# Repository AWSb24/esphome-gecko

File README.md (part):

Home Assistant integration for Gecko spa systems. The ESP32 drives the spa's 5V I2C bus directly through a bidirectional logic level converter - no Arduino in the middle. The reference build uses a Seeed Studio XIAO ESP32-C3. Tested together with a Gecko IN.YE-3-H3.0 (YE-3-CE) spa controller. Feel free to combine with my home assistant integration for smart heating based on electricty price [Smart Spa Heating Integration](https://github.com/zteifel/smart-spa-heating).

## In this fork (in.YE-5 support)

This fork builds on kcembrey's `direct-i2c` branch and adds what an **in.YE-5-H3.0** (config 65 / status 66) needs once the in.touch 2 cloud module is retired:

| Feature | What it does | Docs |
|---|---|---|
| Clock sync | Keeps the spa's clock set from SNTP or Home Assistant, which the in.touch used to do | [Clock sync](#clock-sync) |
| Keypad lock | UNLOCK / PARTIAL / FULL as a select in Home Assistant | [Keypad lock](#keypad-lock) |
| ISO1540 isolation | Galvanic isolation between ESP32 and spa bus instead of a BSS138 level converter | [in.YE-5 with an ISO1540 isolator](#inye-5-with-an-iso1540-isolator) |
| WT32-ETH01 | Wired Ethernet instead of Wi-Fi | [WT32-ETH01 with ATV32 drives](#wt32-eth01-with-atv32-drives-on-the-pumps) |
| Pump drives | Altivar 32 / 320 frequency drives over Modbus RTU for soft start and speed control (three-phase motors only) | [WT32-ETH01 with ATV32 drives](#wt32-eth01-with-atv32-drives-on-the-pumps) |
| Carrier board | KiCad PCB: WT32-ETH01, ISO1540, RS485, CO-port header | [`hardware/`](hardware/) |

Ready-made configs:

| File | Board | Network | Extras |
|---|---|---|---|
| [`esphome/spa-controller-in-ye-5-iso1540.yaml`](esphome/spa-controller-in-ye-5-iso1540.yaml) | ESP32 DevKit + ISO1540 | Wi-Fi | Clock sync, keypad lock |
| [`esphome/spa-controller-wt32-eth01-atv32.yaml`](esphome/spa-controller-wt32-eth01-atv32.yaml) | WT32-ETH01 + ISO1540 + RS485 | Ethernet | Plus 3 pump drives via [`esphome/packages/atv32-pump.yaml`](esphome/packages/atv32-pump.yaml) |

**ESPHome version:** the component is an external component and builds against whatever ESPHome you run. It has been checked with ESPHome 2026.10.2; direct I2C on ESP-IDF needs ESP-IDF 5.4 or newer. To get a clear error on an older install, add `min_version: 2026.10.0` under `esphome:`.

On the in.YE-5 the commands use geckolib's SET_VALUE / KEY_PRESS payloads with the pack's own config/status versions, and the memory map matches geckolib's `inyt-cfg-65` / `inyt-log-66`. Status, setpoint, light and pumps 1-3 decode as on the in.YE-3; control from the ESP32 is still to be confirmed on a running in.YE-5.

## Architecture

```
┌──────────────────┐              ┌──────────────────┐             ┌─────────────┐
│      ESP32       │   3.3V I2C   │  Level Converter │   5V I2C    │  Gecko Spa  │
│                  │◄────────────►│    (BSS138 x2)   │◄───────────►│             │
│ - I2C slave      │  SDA / SCL   │                  │   (0x17)    │             │
│   (listening)    │              │  Bidirectional,  │             │             │
│ - I2C master     │              │  open-drain safe │             │             │
│   (short bursts) │              │                  │             │             │
│ - Protocol logic │              │                  │             │             │
│ - Home Assistant │              │                  │             │             │
│ - OTA updates    │              │                  │             │             │
└──────────────────┘              └──────────────────┘             └─────────────┘
```

**Key Design Decision:** The Gecko bus is multi-master and both ends answer to address `0x17`, so the ESP32 cannot stay in one role. It sits in I2C **slave** mode listening to the spa, and flips to **master** mode for the few milliseconds it takes to push a command or a handshake ACK out, then goes straight back to listening. That is exactly what the Arduino proxy used to do internally - it now happens on the ESP32 itself, and all protocol encoding/decoding stays where it always was, on a chip you can update over WiFi (OTA).

Dropping the Arduino also removes the failure mode where the spa restarts but the Arduino does not (or the other way round) and the link stays dead until something power-cycles the proxy. There is no second processor to fall out of sync: when the bus goes quiet the ESP32 reinitialises its own I2C peripheral, which includes the standard nine-clock bus recovery.

> **Still running the Arduino proxy?** It is still supported - see [Legacy: Arduino I2C Proxy](#legacy-arduino-i2c-proxy).

## Table of Contents

1. [Installation](#installation)
2. [Hardware Build](#hardware-build)
3. [Configuration Reference](#configuration-reference)
4. [I2C Protocol](#i2c-protocol)
5. [Legacy: Arduino I2C Proxy](#legacy-arduino-i2c-proxy)
6. [Buy me a coffee](#buy-me-a-coffee)
7. [TODO](#todo)
8. [Troubleshooting](#troubleshooting)
9. [Credits](#credits)

---

## Installation

### Quick Start

1. **Set up hardware** - See [Hardware Build](#hardware-build) section below

2. **Nothing to flash but the ESP32** - the level converter is passive. If you are migrating from the Arduino proxy, unplug the Arduino and wire the converter in its place; see [Hardware Build](#hardware-build).

3. **Create a secrets.yaml file** with your credentials:
   ```yaml
   wifi_ssid: "YourWiFiName"
   wifi_password: "YourWiFiPassword"
   api_encryption_key: "generate-with-openssl-rand-base64-32"
   ota_password: "your-ota-password"
   ```
   Generate the API key with: `openssl rand -base64 32`

4. **Create your ESPHome configuration** - This component can be installed directly from GitHub:

```yaml
substitutions:
  device_name: spa-controller

esphome:
  name: ${device_name}
  friendly_name: Spa Controller

esp32:
  # Seeed Studio XIAO ESP32-C3 - the generic C3 definition works for it
  board: esp32-c3-devkitm-1
  framework:
    type: arduino  # esp-idf works too - see Configuration Reference

# Import Gecko Spa component from GitHub
external_components:
  - source: github://zteifel/esphome-gecko
    components: [gecko_spa]

logger:
  level: DEBUG

wifi:
  ssid: !secret wifi_ssid
  password: !secret wifi_password

api:
  encryption:
    key: !secret api_encryption_key

ota:
  platform: esphome
  password: !secret ota_password

# Gecko Spa component - direct connection to the spa I2C bus.
# XIAO D0/D2. See Hardware Build for why these and not D4/D5.
gecko_spa:
  id: spa
  sda: GPIO2
  scl: GPIO4

# Climate control
climate:
  - platform: gecko_spa
    gecko_spa_id: spa
    name: "Spa"

# Switches
switch:
  - platform: gecko_spa
    gecko_spa_id: spa
    type: light
    name: "Spa Light"
    icon: "mdi:lightbulb"

  - platform: gecko_spa
    gecko_spa_id: spa
    type: pump1
    name: "Spa Pump"
    icon: "mdi:pump"

  - platform: gecko_spa
    gecko_spa_id: spa
    type: circulation
    name: "Spa Circulation"
    icon: "mdi:rotate-3d-variant"

# Program selector
select:
  - platform: gecko_spa
    gecko_spa_id: spa
    name: "Spa Program"
    icon: "mdi:format-list-bulleted"

# Status sensors
binary_sensor:
  - platform: gecko_spa
    gecko_spa_id: spa
    type: standby
    name: "Spa Standby"
    icon: "mdi:power-standby"

  - platform: gecko_spa
    gecko_spa_id: spa
    type: connected
    name: "Spa Connected"
    device_class: connectivity

# Spa internal clock and maintenance reminder due dates
text_sensor:
  - platform: gecko_spa
    gecko_spa_id: spa
    type: spa_time
    name: "Spa Time"
    icon: "mdi:clock-outline"

  - platform: gecko_spa
    gecko_spa_id: spa
    type: rinse_filter
    name: "Rinse Filter Due"
    icon: "mdi:air-filter"

  - platform: gecko_spa
    gecko_spa_id: spa
    type: clean_filter
    name: "Clean Filter Due"
    icon: "mdi:air-filter"

  - platform: gecko_spa
    gecko_spa_id: spa
    type: change_water
    name: "Change Water Due"
    icon: "mdi:water-sync"

  - platform: gecko_spa
    gecko_spa_id: spa
    type: spa_checkup
    name: "Spa Checkup Due"
    icon: "mdi:wrench-clock"
```

5. **Flash and add to Home Assistant**:
   ```bash
   esphome run your-config.yaml
   ```

6. The device will appear in Home Assistant under **Settings → Devices & Services → ESPHome**

### Home Assistant Entities

After installation, you'll have these entities:

| Entity | Type | Description |
|--------|------|-------------|
| Spa | Climate | Temperature control with current/target display |
| Spa Light | Switch | Control spa light |
| Spa Pump 1 | Switch | Control main pump |
| Spa Circulation | Switch | Control circulation pump |
| Spa Program | Select | Choose program (Away, Standard, Energy, Super Energy, Weekend) |
| Spa Keypad Lock | Select | UNLOCK / PARTIAL / FULL (`type: lock`) |
| Set Spa Clock | Button | `id(spa).sync_clock()` - with `clock_sync` configured |
| Spa Standby | Binary Sensor | Standby mode status |
| Spa Connected | Binary Sensor | Connection status to spa |
| Spa Time | Text Sensor | Spa's internal clock (DD/MM HH:MM:SS) |
| Spa Rinse Filter Due | Text Sensor | Due date for filter rinse (YYYY-MM-DD) |
| Spa Clean Filter Due | Text Sensor | Due date for filter clean (YYYY-MM-DD) |
| Spa Change Water Due | Text Sensor | Due date for water change (YYYY-MM-DD) |
| Spa Checkup Due | Text Sensor | Due date for spa checkup (YYYY-MM-DD) |
| Refresh Spa Status | Button | Manually request status update |
| Reconnect Spa Bus | Button | Reinitialise the I2C peripheral and recover the bus |

---

## Hardware Build

The reference build is a **Seeed Studio XIAO ESP32-C3**. Other ESP32 boards work too - see [Other boards](#other-boards).

### Components Required

| Component | Description | Notes |
|-----------|-------------|-------|
| Seeed Studio XIAO ESP32-C3 | WiFi microcontroller | Reference board. Any ESP32 works, on either framework |
| Bidirectional logic level converter | 3.3V <-> 5V, 2 channels minimum | **Must be the MOSFET (BSS138) type.** See the warning below |
| 2 x 220Ω resistors | Series protection for the I2C pins | Recommended - see [Protecting the ESP32 pins](#protecting-the-esp32-pins) |
| Dupont wires | Various | Connections between board, converter and spa |

> **The converter type matters.** I2C is an open-drain bus: both ends pull the line low and pull-up resistors bring it back high. Only the passive MOSFET converters (BSS138, or a TXS010x) can pass that. A push-pull converter such as the **TXB0104 will not work** on I2C, and neither will a resistor voltage divider - that is fine for one-way UART, but it cannot pass a line the far end is holding down.

### Pin Connections

#### XIAO ESP32-C3 to Level Converter (low-voltage side)

| XIAO Pin | GPIO | Converter Pin | Notes |
|----------|------|---------------|-------|
| D0 | GPIO2 | LV1 | I2C data (SDA), via 220Ω |
| D2 | GPIO4 | LV2 | I2C clock (SCL), via 220Ω |
| 3V3 | - | LV | Reference for the low side. **Must be 3.3V, never 5V** |
| GND | - | GND | Common ground |

#### Level Converter to Spa (high-voltage side)

Pin numbers are on the spa's CO port, as shown in the pinout picture below.

| Converter Pin | Spa CO Port | Notes |
|---------------|-------------|-------|
| HV1 | SDA (pin 3) | I2C data, 5V side |
| HV2 | SCL (pin 2) | I2C clock, 5V side |
| HV | 5V (pin 4) | Reference for the high side |
| GND | GND (pin 8) | Common ground required |

**Why D0/D2 and not D4/D5?** D4/D5 (GPIO6/GPIO7) are the XIAO's labelled SDA/SCL, and on a healthy board they are the better choice because they are not strapping pins. The reference build moved to D0/D2 after GPIO6/GPIO7 were damaged by 5V from the old Arduino proxy wiring. GPIO2 is a C3 strapping pin, so ESPHome prints a warning about it; the I2C pull-ups hold it high at reset, which is the state it needs.

**Pull-ups:** the spa bus already carries its own pull-ups to 5V, and BSS138 breakout boards carry 10k pull-ups on both sides. Do not add more.

**Power:** the spa's 5V rail can supply the converter's HV reference, but do not run the ESP32 off it - the spa rates that line at 125mA, and WiFi bursts go above that. Use USB or a separate supply.

### Protecting the ESP32 pins

A correctly wired BSS138 never lets the ESP32 side rise above its 3.3V reference, so the pins are safe by design. These guard against the ways that can go wrong:

- **220Ω in series with each I2C line, at the ESP32 end.** If 5V ever reaches the line, this limits the current into the pin's clamp diodes to a few mA, which the pin survives. It makes no practical difference to I2C at 100kHz. Stay at 220Ω or below: when the ESP32 pulls the line low, the spa-side pull-up current flows through this resistor too, and a larger value lifts the "low" voltage.
- **Meter the converter before connecting the ESP32.** LV must read 3.3V and HV 5V. LV accidentally on 5V is the one miswiring that puts 5V straight onto the ESP32 pins through the converter's pull-ups.
- **Optional: a TVS/ESD array (~5-6V, e.g. SRV05-4) on the spa side**, where the cable lands. Pumps and heaters make a spa an electrically noisy place, and Gecko's own in.touch-2 uses a TVS plus series resistors (see the note in the pinout picture).
- **Optional: full galvanic isolation.** An **ISO1540** or **ADuM1250** can replace the BSS138: it level-shifts and isolates, so the spa and ESP32 grounds are no longer joined. Use those parts, **not the ISO1541/ADuM1251**, which pass SCL in one direction only - the spa drives the clock too, so they would break this multi-master bus. Their ESP32-side low level also sits a little above 0V by design, so bench-test before sealing the enclosure.

### Wiring Diagram
Credits to agittins for the pictures

```
              ┌────────────────────────────────┐
              │   Gecko Spa CO port (pin no.)  │
              │                                │
              │    SDA     SCL     5V     GND  │
              │    (3)     (2)     (4)    (8)  │
              └─────┬───────┬───────┬──────┬───┘
                    │       │       │      │
              ┌─────┴───────┴───────┴──────┴───┐
              │    HV1     HV2     HV     GND  │
              │      Logic Level Converter     │
              │     (BSS138, bidirectional)    │
              │    LV1     LV2     LV     GND  │
              └─────┬───────┬───────┬──────┬───┘
                    │       │       │      │
                 [220Ω]  [220Ω]     │      │
                    │       │       │      │
              ┌─────┴───────┴───────┴──────┴───┐
              │    D0      D2     3V3     GND  │
              │  (GPIO2) (GPIO4)               │
              │      Seeed XIAO ESP32-C3       │
              └────────────────────────────────┘
```

### Other boards

Direct I2C works on any ESP32, with either framework. These example configs compile but have not been run against a spa:

- [`esphome/spa-controller-feather-s2.yaml`](esphome/spa-controller-feather-s2.yaml) - Adafruit Feather ESP32-S2 on GPIO3/GPIO4 (the pins labelled SDA/SCL). That board gates power to its on-board I2C pull-ups behind GPIO7, which the config drives high on boot.
- [`esphome/spa-controller-olimex.yaml`](esphome/spa-controller-olimex.yaml) - Olimex ESP32-POE-ISO on GPIO13/GPIO14. See [the Olimex guide](docs/olimex-poe-setup.md).
- [`esphome/spa-controller-in-ye-5-iso1540.yaml`](esphome/spa-controller-in-ye-5-iso1540.yaml) - ESP32 DevKit on GPIO21/GPIO22 behind an ISO1540 isolator. See [in.YE-5 with an ISO1540 isolator](#inye-5-with-an-iso1540-isolator).
- [`esphome/spa-controller-wt32-eth01-atv32.yaml`](esphome/spa-controller-wt32-eth01-atv32.yaml) - WT32-ETH01 on IO4/IO32 behind an ISO1540, with RS485 for pump drives. See [WT32-ETH01 with ATV32 drives](#wt32-eth01-with-atv32-drives-on-the-pumps) and the carrier board in [`hardware/`](hardware/).

---

## Configuration Reference

### `gecko_spa` options

| Option | Default | Description |
|--------|---------|-------------|
| `sda` | *(required for direct I2C)* | GPIO carrying I2C data to the level converter |
| `scl` | *(required for direct I2C)* | GPIO carrying I2C clock to the level converter |
| `i2c_bus` | `0` | Which I2C peripheral to use. Change it only if something else in your config already claims bus 0. The ESP32-C3 has only one, so it must be `0` there |
| `address` | `0x17` | Bus address. Both the spa and the controller answer to this |
| `frequency` | `100kHz` | Bus speed. The spa runs standard mode; leave it alone unless you know otherwise |
| `notif_date_format` | `D-M-Y` | Swap to `Y-M-D` if the maintenance reminder dates look wrong |
| `min_temperature` | `26°C` | Lowest setpoint Home Assistant will offer and send, down to `10°C` |
| `max_temperature` | `40°C` | Highest setpoint Home Assistant will offer and send, up to `41.1°C` (106 °F). Gecko panels only go above 40 °C by holding the up key |
| `quiet_time` | - | Hold the pumps off every night - see [Quiet time](#quiet-time) |
| `clock_sync` | - | Keep the spa's clock set from an ESPHome time source - see [Clock sync](#clock-sync) |
| `uart_id` | - | Legacy Arduino proxy mode. Mutually exclusive with `sda`/`scl` |
| `reset_pin` | - | Legacy Arduino proxy mode only - the GPIO wired to the Arduino's RST pin |

Direct I2C mode works on both ESP32 frameworks, and picks the I2C slave backend to match:

| Framework | Backend | Notes |
|-----------|---------|-------|
| `arduino` | The Arduino core's I2C slave HAL | The one the reference build has been run against a spa on |
| `esp-idf` | ESP-IDF's I2C slave driver, version 2 | Needs ESP-IDF 5.4 or newer. On 5.x the component enables `CONFIG_I2C_ENABLE_SLAVE_DRIVER_VERSION_2` itself: version 1 cannot tell where one transaction ends and the next begins, and this protocol identifies messages by their length. ESP-IDF 6 has only version 2, the same API, so nothing needs enabling there |

The `Transport:` line in the boot log says which one is running. On a XIAO ESP32-C3, esp-idf builds about 54 KB smaller in flash and saves about 3 KB of RAM.

**Switching an existing device between frameworks:** both frameworks give the app the same two OTA slots, at the same size and position, so an OTA update can carry the switch. OTA never rewrites the partition table, though, so the device keeps its old table until its next USB flash. That is harmless: the only differences come after the app slots (the Arduino layout has a slightly smaller NVS plus two partitions the esp-idf build ignores).

### Lambdas

| Call | Description |
|------|-------------|
| `id(spa).request_status()` | Send a GO immediately, prompting a fresh handshake and status dump |
| `id(spa).recover_link()` | Reinitialise the link: I2C peripheral reset (direct mode) or Arduino reset pulse (proxy mode) |
| `id(spa).reset_arduino()` | Alias of `recover_link()`, kept so older configs keep working |
| `id(spa).pause_quiet_time(120)` | Let the pumps run for the next 120 minutes even inside quiet time; `0` resumes quiet time now |
| `id(spa).start_quiet_time(120)` | Start quiet time now, outside the window too, for the next 120 minutes (a run that reaches the window carries on into it); `0` goes back to the schedule |
| `id(spa).sync_clock()` | Set the spa's clock from the `clock_sync` time source now |
| `id(spa).send_lock_command(1)` | Keypad lock: `0` unlocked, `1` partial, `2` full |
| `id(spa).hold_standby(15)` | Hold the spa in standby for the next 15 minutes, whatever the time; call again to extend, `0` releases - see [Standby hold](#standby-hold) |

### Quiet time

Outside its filter cycles a spa still runs its pumps now and then, mostly to circulate water past the heater's temperature probe. The only way to stop that is standby - the panel's Maintenance mode, which turns every pump off for a while (30 minutes from the panel). Quiet time puts the spa into that same standby every night and keeps it there:

```yaml
gecko_spa:
  # ...
  quiet_time:
    time_id: ha_time       # your time: component; optional if you have just one
    start: "21:00"
    end: "09:00"
    min_water_temperature: 10°C   # optional, default 10°C
```

- Each standby runs on the spa's own timer for 60 minutes and is topped up before it ends, so a crash or reboot can never keep the pumps off for more than an hour.
- At `end` - or when paused - quiet time takes the spa out of the standby it started. It never ends a Maintenance run you started from the panel outside quiet time.
- **Standby stops the heater too.** The water cools overnight and heats again after `end`. If it ever falls below `min_water_temperature`, quiet time gives up until the next night.
- Turn on a pump during quiet time and quiet time will put the spa back in standby within about a minute. Pause it first.

Buttons to pause it or start it early, and a sensor showing whether it is in force:

```yaml
button:
  - platform: template
    name: "Spa Quiet Time Off (2 h)"
    icon: "mdi:volume-high"
    on_press:
      - lambda: id(spa).pause_quiet_time(120);

  - platform: template
    name: "Spa Quiet Time On (2 h)"     # start it early, or for a while during the day
    icon: "mdi:sleep"
    on_press:
      - lambda: id(spa).start_quiet_time(120);

binary_sensor:
  - platform: gecko_spa
    gecko_spa_id: spa
    type: quiet_time
    name: "Spa Quiet Time"
```

Quiet time needs the standby timer's position in the status block, which is mapped for status version 51 and later.

### Standby hold

`hold_standby(minutes)` puts the spa in the same standby on demand - for example to shed load when a battery inverter is close to its limit, since standby stops the heater (about 4 kW on a 240 V pack) and every pump. Each call extends the hold; `0` releases it. A hold that is not renewed lapses by itself, so a lost release never keeps the spa off for long.

Expose it to Home Assistant as an action, plus a sensor showing when a hold is in force:

```yaml
api:
  actions:
    - action: spa_standby_hold          # esphome.<device name>_spa_standby_hold in Home Assistant
      variables:
        minutes: int
      then:
        - lambda: id(spa).hold_standby(minutes);

binary_sensor:
  - platform: gecko_spa
    gecko_spa_id: spa
    type: standby_hold
    name: "Spa Standby Hold"
```

A hold works with or without `quiet_time`. Releasing it takes the spa out of standby only if the hold put it there and quiet time does not want it: a Maintenance run started from the panel is left alone.

### Water-care programs

On spas whose panel has water-care programs (Away, Standard, Energy, Super Energy, Weekend), each with its own filter times and days, the program - not the spa's internal filter schedule - starts and stops filtration. The spa reports this as `FilterAccess = REMOTE`. The program schedules themselves live in the panel, which the ESP32 cannot see from the spa's communication port, so they cannot be read or edited from Home Assistant.

What you can do from Home Assistant:

- **Switch program** with the `select` platform.
- **See what the program is doing**, read-only:

```yaml
text_sensor:
  - platform: gecko_spa
    gecko_spa_id: spa
    type: filtration          # Idle / Stop / Start / New / Active
    name: "Spa Filtration"

sensor:
  - platform: gecko_spa
    gecko_spa_id: spa
    type: filter_time_left    # minutes left in the current filter run
    name: "Spa Filter Time Left"

binary_sensor:
  - platform: gecko_spa
    gecko_spa_id: spa
    type: economy             # economy (lower setpoint) in effect
    name: "Spa Economy"
```

These read fields that sit at the same positions in every inYT status version from 51 through 83.

### Clock sync

The in.touch sets the spa's clock whenever it connects. Without it the clock drifts, and the spa's own filter and economy schedules run on that clock. `clock_sync` takes over:

```yaml
time:
  - platform: sntp          # or homeassistant
    id: spa_clock
    timezone: Europe/Berlin

gecko_spa:
  # ...
  clock_sync:
    time_id: spa_clock
    max_drift: 2min         # default; minimum 10s
```

The spa reports its clock in the 'K' message during each handshake. If that is more than `max_drift` off the time source, the component sets it (at most once per 10 minutes), and it sets it once a day regardless. The command is `4B YY MM DD DoW HH MM SS` (day of week 0 = Sunday), taken from the LDWTH fork. The date byte order has not yet been checked against an in.touch capture on an in.YE-5, so check the `Spa Time` text sensor after the first sync.

### Keypad lock

```yaml
select:
  - platform: gecko_spa
    gecko_spa_id: spa
    type: lock              # UNLOCK / PARTIAL / FULL
    name: "Spa Keypad Lock"
```

Writes geckolib's `LockMode` (position 0x0136 on status v51+). The select follows the spa's status, so it snaps back if the spa ignores the change. `type: program` (the default) is the water-care program select.

### in.YE-5 with an ISO1540 isolator

[`esphome/spa-controller-in-ye-5-iso1540.yaml`](esphome/spa-controller-in-ye-5-iso1540.yaml) is a full config for an in.YE-5-H3.0 (config 65, status 66) on an ESP32 DevKit, isolated from the spa with an ISO1540 instead of a level converter. Wiring:

| CO port pin | Signal | ISO1540 (side 2) |
|---|---|---|
| 8 | GND | GND2 |
| 4 | 5V | VCC2 |
| 3 | SDA | SDA2 |
| 2 | SCL | SCL2 |
| 6 | 12V | not used |

ESP32 3V3/GND/GPIO21/GPIO22 go to VCC1/GND1/SDA1/SCL1, with 4.7k pull-ups to 3V3 on side 1 if the module has none. Use the ISO1540, not the ISO1541: the ISO1541's SCL is one-way, and the ESP32 drives SCL when it sends commands. Power the ESP32 from its own USB supply so nothing bridges the isolation.

Notes from bus captures on this pack, where the in.touch 2 was the only other controller:

- The I2C payloads are geckolib's SPACK payloads. KEY_PRESS (`39 kk`) and SET_VALUE (`46 cfg log pos16 data`) both appear, with positions matching geckolib's `inyt-cfg-65` / `inyt-log-66`.
- The in.touch drove filtration and economy remotely (`FilterAccess`/`EconomyAccess` = REMOTE at 0x0106, starting runs with `RemoteFiltAction`/`RemoteEconAction`). Check the `Filtration` sensor after removing the in.touch to confirm filter runs still start.
- Temperature units: position 0x0021, `00` = °F, `01` = °C.

### WT32-ETH01 with ATV32 drives on the pumps

[`esphome/spa-controller-wt32-eth01-atv32.yaml`](esphome/spa-controller-wt32-eth01-atv32.yaml) runs the same in.YE-5 setup on a WT32-ETH01 (wired Ethernet, LAN8720). It also drives the three pumps through Schneider Altivar 32 frequency drives over Modbus RTU, which gives them a soft start and stop and an adjustable speed. The wiring and drive settings are in the file header.

| WT32-ETH01 | Goes to |
|---|---|
| IO4 / IO32 | ISO1540 SDA1 / SCL1 |
| IO17 / IO5 / IO33 | RS485 transceiver DI / RO / DE+RE |

Each pump comes from [`esphome/packages/atv32-pump.yaml`](esphome/packages/atv32-pump.yaml), included once per drive with its pump number and Modbus address. The spa pack stays in charge:

- **Start:** when the pack switches a pump on (from the panel, Home Assistant, filtration or heating), the drive gets the speed from `Pumpe N Drehzahl` and starts on its ACC ramp.
- **Stop:** when the pack switches the pump off, the drive stops on its dEC ramp.
- **Resync:** a 10 s check repeats a lost start or stop.
- **Fail-safe:** if the ESP32 stops talking, the drive's Modbus timeout (ttO) trips and the pump stops.
- **Entities per pump:** output frequency, motor current, fault flag, last fault code, and a fault-reset button.

Before wiring this up:

- **Motors.** The ATV32 has a three-phase output. Many spa pumps (e.g. LX LP300, "PH1" on the plate) are single-phase capacitor motors, and those must not run on a drive. Their terminal box looks the same as a three-phase motor in Steinmetz connection, so measure: with mains and capacitor disconnected, three equal resistances between the terminal pairs mean a three-phase delta winding; one reading equal to the sum of the other two means single-phase.
- **Drive size.** Pick the drive by the motor's current, not its kW. A three-phase motor that must stay in 230 V delta runs on a 400 V drive (ATV320...N4) with UnS = 230 V and FrS = 50 Hz, sized for the delta current (for 10 A, an ATV320U55N4C). Save the settings with SCS so a factory reset cannot put 400 V on the windings. If the plate says 230Δ/400Y and the box can be rebridged, star connection on an ATV320U30N4C with UnS = 400 V is cleaner.
- **Power path.** Each drive needs permanent mains, with the motor on its output. The pack's pump relay no longer feeds the motor; never switch a drive's input or output with a relay to run the pump.
- **RCD.** Drives leak DC fault current, so the spa circuit needs a type B (or F) 30 mA RCD. Have an electrician do the mains side.
- **Registers.** The registers used are CMD 8501, LFR 8502, ETA 3201, RFR 3202, LCR 3204 and LFT 7121. Check them against the ATV32 communication parameters for your firmware. The ATV320, the ATV32's successor, uses the same registers.

---

## I2C Protocol

### Overview

The Gecko spa uses I2C for communication between components. The spa motherboard and external controllers share address **0x17** in a multi-master configuration.

### Bus Configuration

| Parameter | Value |
|-----------|-------|
| I2C Address | 0x17 (23 decimal) |
| Bus Speed | 100kHz (standard mode) |
| Configuration | Multi-master |
| Pull-ups | 4.7kΩ (typically on spa bus) |

### Multi-Master Operation

Both the spa motherboard and the Arduino controller use address 0x17. The spa sends status updates to this address, and the controller sends commands to this address. This allows bidirectional communication without address conflicts.

### Message Checksums

Most messages use XOR checksum of bytes 0 to (length-2), stored in the last byte.

```c
uint8_t calcChecksum(uint8_t* data, uint8_t len) {
    uint8_t xorVal = 0;
    for (uint8_t i = 0; i < len - 1; i++) {
        xorVal ^= data[i];
    }
    return xorVal;
}
```

---

### Messages FROM Spa (Status Updates)

#### GO Keep-Alive & Handshake Protocol

The controller sends GO every 60 seconds to trigger a handshake sequence.

**GO Message (15 bytes):**
```
17 00 00 00 00 17 09 00 00 00 00 00 01 47 4F
                                       ^^^^
                                       "GO" ASCII
```

**Handshake Sequence:**
After GO is sent, the spa responds with messages that must be acknowledged:

1. **Spa sends 33-byte config message** (contains XML filename like `inYT_C82.xml`)
2. **Controller replies with ACK** (15 bytes): `17 0A 00 00 00 17 09 00 00 00 00 00 01 00 02`
3. **Spa sends another 33-byte config message**
4. **Controller replies with ACK**
5. **Spa sends 22-byte clock message** (byte[13] = 0x4B = 'K', contains date/time)
   - Byte 15: Day (decimal)
   - Byte 16: Month (decimal)
   - Byte 17: Day of week (0=Sun)
   - Byte 18: Hour (hex, 24h format)
   - Byte 19: Minutes (hex)
   - Byte 20: Seconds (hex)
   - Byte 21: Checksum
6. **Controller replies with ACK**
7. **Spa sends 15-byte "LO" message**: bytes[13-14] = 0x4C 0x4F = "LO"
8. **Handshake complete** - status messages now flow normally

**Important:** Without proper handshake acknowledgment, commands may not receive immediate status responses.

#### Status Message (Multi-Part, 162 bytes concatenated)

Status data is sent as a **multi-part message** split across 3 I2C transmissions.

**Multi-Part Message Structure:**

| Part | Raw Size | Header | Payload | Description |
|------|----------|--------|---------|-------------|
| 1 | 78 bytes | 16 bytes | 62 bytes | First status part |
| 2 | 78 bytes | 16 bytes | 62 bytes | Second status part |
| 3 | 54 bytes | 16 bytes | 38 bytes | Final status part |
| **Total** | 210 bytes | 48 bytes | **162 bytes** | Concatenated payload |

**Continuation Flag (Byte 9 in raw message):**
- `0x01` = More parts coming
- `0x00` = Last part of message

**Header (16 bytes, stripped from each part):**
```
17 09 00 00 00 17 0A 01 00 XX 00 00 YY ZZ 52 51
```
Where XX = continuation flag (byte 9), YY ZZ = length/type info

**Part payload:** a big-endian word giving the pack memory position of the part's first byte, the data, then a checksum byte. Status parts start at position 256 (`01 00`), config parts at 0. Parts need not be contiguous: an inYT C65 config message carries positions 0, 59, 118 and 448, then its status block at 256, 315 and 374. So the component reads fields by position. Some packs send the same part several times, sometimes with fresher data, and resend the final part after the message is complete; the component keeps one copy of each. A part for position 0, or for a position already received, means the spa abandoned the message in progress and started a new one.

**Message Identification (in concatenated 162-byte payload):**
- Byte[1] = 0x00 indicates status data

**Key Byte Positions (VERIFIED in 162-byte concatenated payload):**

| Byte | Description | Values |
|------|-------------|--------|
| 1 | Data type | 0x00 = Status data |
| 3 | Standby | 0x03 = Standby ON |
| 5 | Pump state | 0x02 = Pump ON |
| 6 | Heat flags | Bit 7 (0x80) = Circ during heating, Bit 5 (0x20) = Heating |
| 7 | Pump flag | 0x01 = Pump ON |
| 21-22 | Target temp (raw) | Big-endian, divide by 18.0 for °C |
| 23-24 | Actual temp (raw) | Big-endian, divide by 18.0 for °C |
| 26 | Heating flag | Bit 2 (0x04) = Heating |
| 53 | Light state | 0x01 = Light ON |
| 112 | Circulation | 0x01 = Circulation ON (manual toggle) |

**Example:** Raw temp bytes `02 9A` = 0x029A = 666 / 18.0 = **37.0°C**

#### Configuration Message (Multi-Part, 405 bytes concatenated)

Periodic configuration/settings dump sent by the spa, typically after handshake.

**Multi-Part Message Structure:**

Similar to status messages, this is sent as multiple I2C transmissions with 16-byte headers stripped and payloads concatenated to form a 405-byte message.

**Known Byte Positions (PARTIALLY DECODED):**

| Byte | Description | Values |
|------|-------------|--------|
| 3-4 | Target temperature (raw) | Big-endian, divide by 18.0 for °C |

**Example:** Bytes 3-4 = `02 9A` = 0x029A = 666 / 18.0 = **37.0°C**

**Note:** This message likely contains program schedules, filter cycle settings, notification intervals, and other configuration data. Further reverse engineering is needed to decode additional fields.

---

#### Program Status Message (18 bytes)

Indicates current program selection.

```
17 0B 00 00 00 17 09 00 00 00 00 00 04 4E 03 D0 [PROG] [CHK]
                                                  ^^^^
                                                  Program ID
```

**Program IDs:**

| ID | Program |
|----|---------|
| 0x00 | Away |
| 0x01 | Standard |
| 0x02 | Energy |
| 0x03 | Super Energy |
| 0x04 | Weekend |

---

#### Notification Message (77 bytes)

Maintenance reminder data, sent with byte[6] = 0x0B.

**Entry Format (6 bytes each, starting at byte 16):**

```
[ID] [DD] [MM] [YY] [INTERVAL_LO] [INTERVAL_HI]
```

| Byte | Description |
|------|-------------|
| ID | Notification type (see below) |
| DD | Reset day (decimal, 1-31) |
| MM | Reset month (decimal, 1-12) |
| YY | Reset year (2-digit, e.g., 25 for 2025) |
| INTERVAL_LO | Interval low byte |
| INTERVAL_HI | Interval high byte |

**Notification IDs:**

| ID | Notification |
|----|--------------|
| 0x01 | Rinse Filter |
| 0x02 | Clean Filter |
| 0x03 | Change Water |
| 0x04 | Spa Checkup |

**Interval:** 16-bit little-endian value representing days between reminders.

**Due Date Calculation:** `due_date = reset_date + interval_days`

**Example:** Entry `01 09 12 25 1E 00` = Rinse Filter, reset Dec 9 2025, interval 30 days → due Jan 8 2026

---

### Messages TO Spa (Commands)

#### On/Off Command (20 bytes)

Controls light, pump, and circulation.

```
17 0A 00 00 00 17 09 00 00 00 00 00 06 46 52 51 01 [FUNC] [STATE] [CHK]
                                                    ^^^^   ^^^^^   ^^^
                                                    Function ID    Checksum
```

**Function IDs:**

| ID | Function | ON State | OFF State |
|----|----------|----------|-----------|
| 0x33 | Light | 0x01 | 0x00 |
| 0x03 | Pump | 0x02 | 0x00 |
| 0x6B | Circulation | 0x01 | 0x00 |

**Note:** Pump uses 0x02 for ON state, not 0x01.

**Example - Light ON:**
```
17 0A 00 00 00 17 09 00 00 00 00 00 06 46 52 51 01 33 01 [CHK]
```

#### Program Select Command (18 bytes)

Changes the spa program.

```
17 0B 00 00 00 17 09 00 00 00 00 00 04 4E 03 D0 [PROG] [CHK]
```

**Pre-calculated Commands:**

| Program | Command (hex) |
|---------|---------------|
| Away | `17 0B 00 00 00 17 09 00 00 00 00 00 04 4E 03 D0 00 9B` |
| Standard | `17 0B 00 00 00 17 09 00 00 00 00 00 04 4E 03 D0 01 9A` |
| Energy | `17 0B 00 00 00 17 09 00 00 00 00 00 04 4E 03 D0 02 99` |
| Super Energy | `17 0B 00 00 00 17 09 00 00 00 00 00 04 4E 03 D0 03 98` |
| Weekend | `17 0B 00 00 00 17 09 00 00 00 00 00 04 4E 03 D0 04 9F` |

#### Temperature Set Command (21 bytes)

Sets the target temperature for the spa. It appears to be one use of the pack's general "write memory" command (`0x46`): after the config and status versions come a 2-byte address and then the value, with the length byte at offset 12 saying how long the value is. The light, pump and circulation commands have the same shape with a 1-byte value. Here the address is `0x0001`, which is `SetpointG` in the config structure.

```
17 0A 00 00 00 17 09 00 00 00 00 00 07 46 [CFG] [STS] 00 01 [HI] [LO] [CHK]
                                          ^^^^^^^^^^^ ^^^^^ ^^^^^^^^^
                                          config and  addr  setpoint
                                          status vers 0x0001  word
```

**Temperature Encoding:** a big-endian 16-bit word in 1/18 °C.

```
RAW = round(temperature_celsius × 18)
```

| Temperature | RAW | Bytes |
|-------------|-----|-------|
| 26.0°C | 468 | `01 D4` |
| 36.5°C | 657 | `02 91` |
| 37.0°C | 666 | `02 9A` |
| 40.0°C | 720 | `02 D0` |
| 41.0°C | 738 | `02 E2` |

> Earlier versions assumed the high byte was always `02` and computed only the low byte as `RAW - 512`. That covers 28.5–42.5 °C; any setpoint below 28.5 °C reached the spa as the wrong value.

Each pack has its own setpoint range (`MinSetpointG`/`MaxSetpointG` in its config), which the log shows once the handshake completes:

```
[I][gecko_spa]: Config: Spa setpoint range 15.0-41.1 C
```

Set `min_temperature` and `max_temperature` to match, and you get a warning in the log if either reaches past the spa's range. Above 40 °C the panel only goes by holding the up key. `max_temperature` stops at 41.1 °C (106 °F), the maximum an inYT pack reports.

**Example - Set 37°C** (config/status versions 65/66, so `41 42`):
```
17 0A 00 00 00 17 09 00 00 00 00 00 07 46 41 42 00 01 02 9A [CHK]
```

-------------|-------------|-----------|
| 26.0°C | (26 × 18) - 512 = -44 | 0xD4 |
| 36.5°C | (36.5 × 18) - 512 = 145 | 0x91 |
| 37.0°C | (37 × 18) - 512 = 154 | 0x9A |
| 40.0°C | (40 × 18) - 512 = 208 | 0xD0 |

**Example - Set 37°C:**
```
17 0A 00 00 00 17 09 00 00 00 00 00 07 46 52 51 00 01 02 9A [CHK]
```

---

## Legacy: Arduino I2C Proxy

The original build put an Arduino Nano between the ESP32 and the spa: the Nano did the I2C, the ESP32 did the protocol, and the two talked over UART. That still works and is still supported by the component - `esphome/spa-controller-arduino-proxy.yaml` is a ready-to-use config.

The direct wiring exists because the proxy has one structural weakness: two processors that must agree on the state of the bus. If the spa restarts and the Arduino does not (or the other way round), the link stays dead until something resets the proxy. With the ESP32 on the bus itself there is no second processor to fall out of sync.

### Migrating to direct I2C

1. Remove the `uart:` block and the `reset_pin:` line from your config.
2. Add `sda:` and `scl:` to `gecko_spa:`.
3. Rewire: the level converter's HV side goes where the Arduino's A4/A5/GND went, its LV side to the ESP32's SDA/SCL/3V3/GND.
4. Flash and unplug the Arduino.

Buttons calling `id(spa).reset_arduino()` keep working - it is now an alias for `recover_link()`.

### Flashing the Arduino Nano

**Option A: Use the precompiled binary (recommended)**

Download `arduino-i2c-proxy-atmega328p.hex` from the [GitHub Releases](https://github.com/zteifel/esphome-gecko/releases) page (or from the `arduino/` folder).

```bash
# Install avrdude (Ubuntu/Debian)
sudo apt install avrdude

# For Nano Clone (new bootloader) - 115200 baud
avrdude -v -patmega328p -carduino -P/dev/ttyUSB0 -b115200 -D -Uflash:w:arduino-i2c-proxy-atmega328p.hex:i

# For Original Arduino Nano (old bootloader) - 57600 baud
avrdude -v -patmega328p -carduino -P/dev/ttyUSB0 -b57600 -D -Uflash:w:arduino-i2c-proxy-atmega328p.hex:i
```

> **Tip:** Most cheap Nano clones from AliExpress/Amazon use the new bootloader (115200 baud). If upload fails, try 57600 baud for original Nanos with the old bootloader.

**Option B: Build from source with PlatformIO**

The Arduino Wire library has a default 32-byte I2C buffer, but the spa sends messages up to 78 bytes. You **must** patch the Wire library to increase this buffer.

1. `pip install platformio`
2. `cd arduino && pio run` to download dependencies
3. Edit `~/.platformio/packages/framework-arduino-avr/libraries/Wire/src/utility/twi.h` and change `#define TWI_BUFFER_LENGTH 32` to `128`
4. `pio run -t upload`

> **Why is patching needed?** The `-DTWI_BUFFER_LENGTH=128` build flag in `platformio.ini` should override this value, but some PlatformIO versions do not apply it correctly. Patching the source file directly ensures the buffer is always 128 bytes.

### Proxy Wiring

#### ESP32-S2 to Arduino Nano Clone (UART + Reset)

| ESP32-S2 Pin | Arduino Nano Clone Pin | Notes |
|--------------|------------------|-------|
| GPIO5 (TX) | RX (D0) | Direct connection (3.3V -> 5V tolerant) |
| GPIO16 (RX) | TX (D1) | Via voltage divider (5V -> 3.3V) - **mandatory** |
| GPIO17 | RST | Via an NPN transistor or spare level-converter channel - **never directly** |
| GND | GND | Common ground required |

> **Do not wire an ESP32 pin straight to the Arduino's RST or TX.** The Nano pulls RST up to 5V, and its TX drives 5V. Either one puts 5V on a 3.3V ESP32 pin; over time that kills the pin, typically with intermittent link failures first. This is exactly how the reference build lost its original RST and RX pins. For RST, use an NPN transistor (ESP32 pin -> 1kΩ -> base, emitter to GND, collector to RST) and set `inverted: true` on `reset_pin`, or route it through a spare channel of a BSS138 level converter.

```
Arduino TX (D1) ----[2.7kΩ]----+---- ESP32 GPIO16 (RX)
                               |
                            [5.6kΩ]
                               |
                              GND
```

Output voltage: ~2.7V (within ESP32 3.3V logic threshold)

#### Arduino Nano Clone to Spa I2C Bus

| Arduino Nano Clone Pin | Spa Connector | Notes |
|------------------|---------------|-------|
| A4 (SDA) | SDA | I2C Data |
| A5 (SCL) | SCL | I2C Clock |
| GND | GND | Common ground |

**Important:** Do NOT connect Arduino VCC to spa - power the Arduino separately via USB or an external supply.

### Proxy Configuration

```yaml
uart:
  id: arduino_uart
  tx_pin: GPIO5
  rx_pin: GPIO16
  baud_rate: 115200
  rx_buffer_size: 512

gecko_spa:
  id: spa
  uart_id: arduino_uart
  reset_pin: GPIO17  # Resets the Arduino automatically on disconnect
```

### UART Proxy Protocol

#### Overview

The Arduino acts as a transparent I2C proxy. The ESP32 sends raw I2C bytes as hex strings, and the Arduino forwards them to the I2C bus. Similarly, I2C messages received by the Arduino are sent to the ESP32 as hex strings.

#### Message Format

- **Baud Rate:** 115200
- **Data Bits:** 8
- **Parity:** None
- **Stop Bits:** 1
- **Line Ending:** `\n` (LF)

#### Commands (ESP32 → Arduino)

| Command | Description |
|---------|-------------|
| `TX:<hex>\n` | Send hex bytes to I2C bus at address 0x17 |
| `PING\n` | Health check |

**Example - Send light ON command:**
```
TX:170A0000001709000000000646525101330163\n
```

#### Responses (Arduino → ESP32)

| Message | Description |
|---------|-------------|
| `I2C_PROXY:V1\n` | Firmware version on boot |
| `READY\n` | Arduino ready for commands |
| `RX:<len>:<hex>\n` | Received I2C message (length in decimal, data in hex) |
| `TX:OK\n` | I2C transmission acknowledged |
| `TX:ERR:INVALID_HEX\n` | Invalid hex string |
| `TX:ERR:TOO_LONG\n` | Message exceeds 128 bytes |
| `PONG\n` | Response to PING |

**Example - Received 78-byte status message:**
```
RX:78:17090000001709...4F\n
```

#### Protocol Logic

All spa protocol logic (GO responses, command encoding, status parsing) runs on the ESP32 in `spa_protocol.h`. This allows OTA updates without physical access to the spa.

---

## TODO

- Scheduling of economy intervals and filter cycles in programs (decoding of i2c protocol complete)
- in.YE-5: confirm the clock-set date byte order against an in.touch reconnect capture
- in.YE-5: confirm filtration still starts once the in.touch (the remote scheduler) is gone
- Cleanup notifications fix

## Troubleshooting

Set `logger: level: DEBUG` and watch the boot log. `dump_config()` prints the transport in use, the pins, the address, and whether I2C slave mode came up.

### "Spa Connected" never turns on

- Check SDA and SCL are not swapped, both through the converter and at the spa connector.
- Confirm the converter is the MOSFET/BSS138 type. A TXB0104 or a resistor divider cannot drive an open-drain bus and will silently fail here.
- Confirm HV is tied to the spa's 5V and LV to the ESP32's 3V3. Without both references a BSS138 board passes nothing.
- Check the ground is common between the ESP32 and the spa.
- On the Adafruit Feather ESP32-S2, make sure GPIO7 (I2C power) is being driven high - the example config does this.
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
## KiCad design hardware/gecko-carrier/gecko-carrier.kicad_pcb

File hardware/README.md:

# Gecko carrier board

Carrier PCB for the [WT32-ETH01 + ATV32 config](../esphome/spa-controller-wt32-eth01-atv32.yaml): a WT32-ETH01 (ESP32 with wired Ethernet) on sockets, the spa's CO port isolated through an ISO1540, an RS485 port for the pump drives and an on-board 230 V power supply.

**Status: v0.1, not built yet.** The board passes DRC and every net is routed, but nobody has made or tested one. Check it in KiCad before you order it.

## What's on it

| Block | Parts | Notes |
|---|---|---|
| Mains | J1 (L, N), F1 T250mA 5x20, RV1 275 VAC varistor, PS1 HLK-PM01 (5 V / 0.6 A) | Left-hand third of the board. 8 mm keep-out band plus a milled slot under PS1 separate it from everything else; closest mains-to-SELV copper is 10 mm. |
| ESP32 | U1 WT32-ETH01 on 2x 1x13 female headers, C1/C2 on 5 V | RJ45 overhangs the bottom edge; the board has a notch under the jack. Powered on its 5V pin only. |
| Programming | J4: GND, TX, RX, IO0, EN | 3.3 V USB-UART adapter. Pull IO0 to GND while resetting to flash. |
| Spa I2C | U2 ISO1540, J2 2x4 IDC header to the Gecko CO port, R1/R2 4k7 pull-ups on the ESP side | Barrier under U2: separate ground pours (GND / GND_SPA) with a keep-out in between. R3/R4 (spa-side pull-ups) are not fitted - the pack has its own. |
| RS485 | U3 MAX3485, D1 SM712, R6/R7 680R bias, R5 120R + JP1 termination, J3 terminal (D1/A+, D0/B-, 0V) | Fit JP1 if the board is at one end of the bus. |

Pin use matches the ESPHome config: I2C SDA IO4, SCL IO32; RS485 TX IO17, RX IO5, DE/RE IO33.

## Before you power it

- **Mains.** Only someone qualified should wire J1. Put the board in a closed, IP-rated enclosure; the spa compartment is damp. Use plastic screws (or no screw) in H4, which sits in the keep-out band.
- **CO-port pinout.** J2 uses the numbering from [`pictures/spa_pinouts.png`](../pictures/spa_pinouts.png): 2 SCL, 3 SDA, 4 5V, 8 GND (6 = 12 V, not used). Before the first connection, measure about 5 V between pins 4 and 8 at the cable end. Mirror the cable if it is the wrong way round.
- **WT32-ETH01 orientation.** Antenna end towards the top (ANT on the silkscreen), RJ45 over the bottom edge.
- **RJ45 notch.** The jack sticks out below the module further than the short header pins next to it (LINK, GND), so the module cannot sit flat on a solid board. The carrier is cut away under the jack (19.2 x 15.6 mm, open to the bottom edge). With the notch the module can be soldered directly; female sockets or long pin headers work as well.

## Files

| Path | What |
|---|---|
| `gecko-carrier/gecko-carrier.kicad_pro` / `.kicad_sch` / `.kicad_pcb` | KiCad 7 project |
| `gecko-carrier/gecko_carrier.kicad_sym`, `gecko_carrier.pretty/` | Project symbols and the WT32-ETH01 footprint |
| `gecko-carrier/fab/gecko-carrier-gerbers.zip` | Gerbers + drill files for a PCB fab (2 layers, 1.6 mm, 120 x 80 mm) |
| `gecko-carrier/fab/bom.csv`, `positions.csv` | Parts list and placement |
| `gecko-carrier/docs/` | Schematic (PDF/PNG) and layer renders |
| `gecko-carrier/drc-report.txt` | DRC result (only cosmetic silkscreen warnings) |
| `tools/` | The generator scripts |

## Regenerating

The schematic, layout and routing are generated from [`tools/parts.py`](tools/parts.py), so a change there (a part, a net, a position) rebuilds everything consistently. Needs KiCad 7 and numpy:

```sh
python3 hardware/tools/gen_sch.py   # schematic (drawn wires, power symbols) + symbol library
python3 hardware/tools/check_sch.py # compares KiCad's netlist of the schematic with parts.py
python3 hardware/tools/gen_pcb.py   # footprints, nets, outline, keep-outs, pours
python3 hardware/tools/route.py     # grid router, pour fill, DRC report
```

The schematic placement and wiring live in `SCH` and `draw()` in `gen_sch.py`; the nets themselves only come from `parts.py`, and `check_sch.py` fails if the drawing connects anything differently.

You can also edit the KiCad files directly. Once you do, stop using the scripts, or they will overwrite your changes.

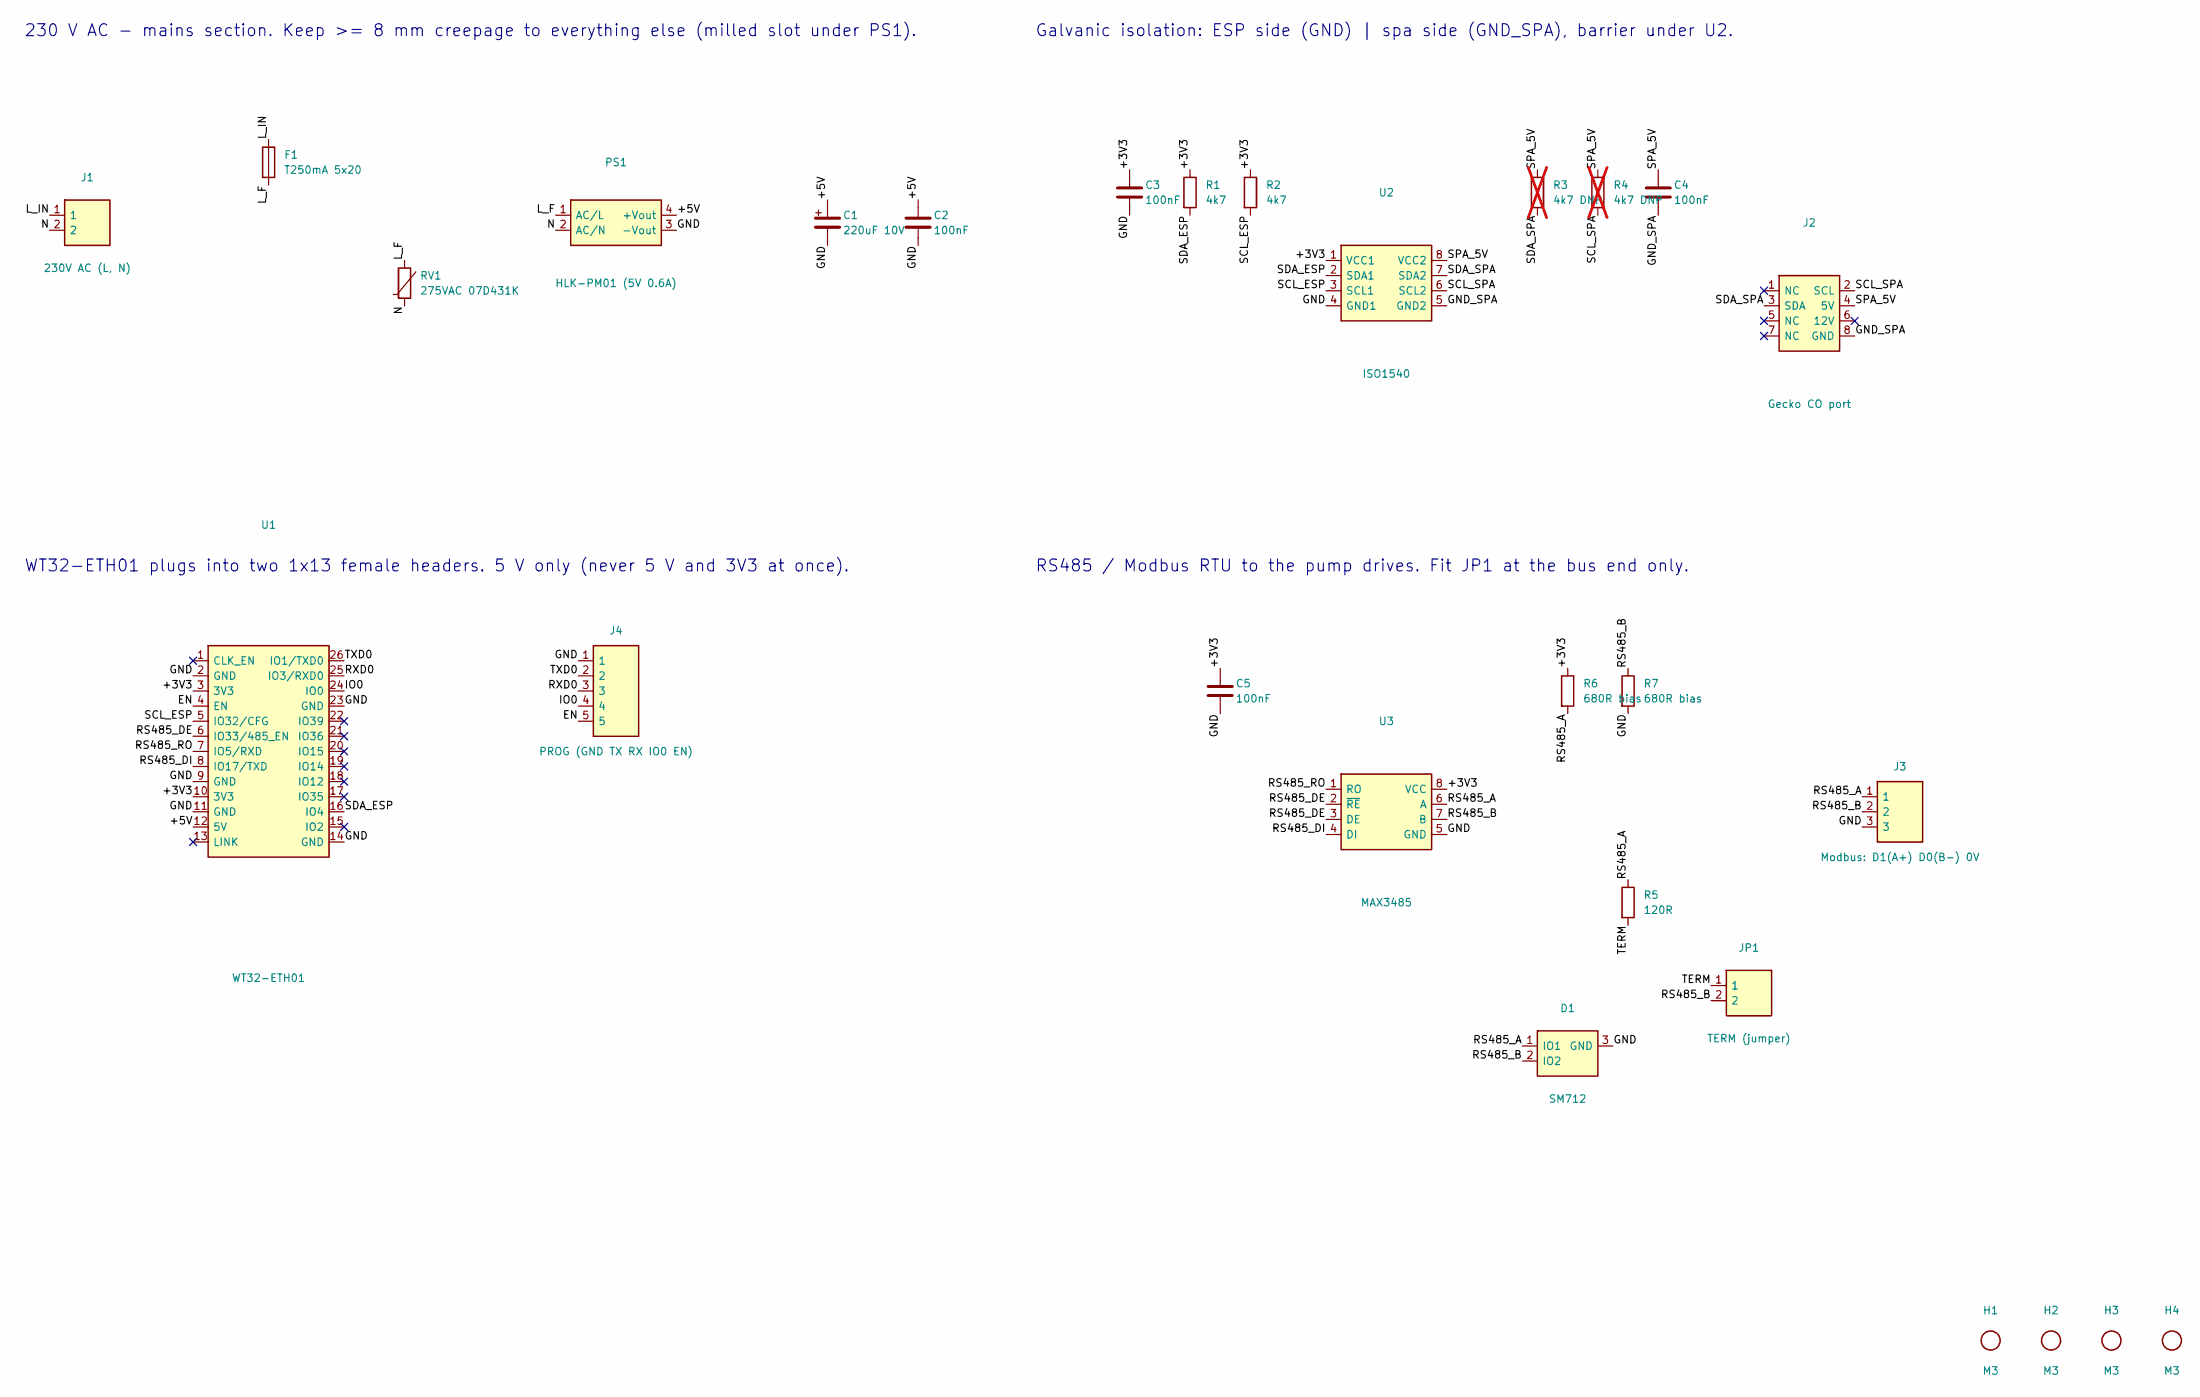
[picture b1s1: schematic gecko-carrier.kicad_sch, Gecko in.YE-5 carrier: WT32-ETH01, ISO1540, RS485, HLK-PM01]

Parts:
C1: 220uF 10V; CP_Radial_D6.3mm_P2.50mm
C2, C3, C4, C5: 100nF; C_0805_2012Metric
D1: SM712; SOT-23
F1: T250mA 5x20; Fuseholder_Clip-5x20mm_Keystone_3517_Inline_P23.11x6.76mm_D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
H1, H2, H3, H4: M3; MountingHole_3.2mm_M3
J1: 230V AC (L, N); TerminalBlock_Phoenix_MKDS-1,5-2-5.08_1x02_P5.08mm_Horizont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
J2: Gecko CO port; IDC-Header_2x04_P2.54mm_Vertical
J3: Modbus: D1(A+) D0(B-) 0V; TerminalBlock_Phoenix_MKDS-1,5-3-5.08_1x03_P5.08mm_Horizont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
J4: PROG (GND TX RX IO0 EN); PinHeader_1x05_P2.54mm_Vertical
JP1: TERM (jumper); PinHeader_1x02_P2.54mm_Vertical
PS1: HLK-PM01 (5V 0.6A); Converter_ACDC_Hi-Link_HLK-PMxx
R1, R2: 4k7; R_0805_2012Metric
R3, R4: 4k7 DNP; R_0805_2012Metric; not fitted
R5: 120R; R_0805_2012Metric
R6, R7: 680R bias; R_0805_2012Metric
RV1: 275VAC 07D431K; RV_Disc_D7mm_W3.5mm_P5mm
U1: WT32-ETH01; WT32-ETH01_Socket
U2: ISO1540; SOIC-8_3.9x4.9mm_P1.27mm
U3: MAX3485; SOIC-8_3.9x4.9mm_P1.27mm

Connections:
+3V3: C3.1, C5.1, R1.1, R2.1, R6.1, U1.3 (3V3), U1.10 (3V3), U2.1 (VCC1), U3.8 (VCC)
+5V: C1.1, C2.1, PS1.4 (+Vout), U1.12 (5V)
EN: J4.5, U1.4 (EN)
GND: C1.2, C2.2, C3.2, C5.2, D1.3 (GND), J3.3, J4.1, PS1.3 (-Vout), R7.2, U1.2 (GND), U1.9 (GND), U1.11 (GND), U1.14 (GND), U1.23 (GND), U2.4 (GND1), U3.5 (GND)
GND_SPA: C4.2, J2.8 (GND), U2.5 (GND2)
IO0: J4.4, U1.24 (IO0)
L_F: F1.2, PS1.1 (AC/L), RV1.1
L_IN: F1.1, J1.1
N: J1.2, PS1.2 (AC/N), RV1.2
RS485_A: D1.1 (IO1), J3.1, R5.1, R6.2, U3.6 (A)
RS485_B: D1.2 (IO2), J3.2, JP1.2, R7.1, U3.7 (B)
RS485_DE: U1.6 (IO33/485_EN), U3.2 (~RE), U3.3 (DE)
RS485_DI: U1.8 (IO17/TXD), U3.4 (DI)
RS485_RO: U1.7 (IO5/RXD), U3.1 (RO)
RXD0: J4.3, U1.25 (IO3/RXD0)
SCL_ESP: R2.2, U1.5 (IO32/CFG), U2.3 (SCL1)
SCL_SPA: J2.2 (SCL), R4.2, U2.6 (SCL2)
SDA_ESP: R1.2, U1.16 (IO4), U2.2 (SDA1)
SDA_SPA: J2.3 (SDA), R3.2, U2.7 (SDA2)
SPA_5V: C4.1, J2.4 (5V), R3.1, R4.1, U2.8 (VCC2)
TERM: JP1.1, R5.2
TXD0: J4.2, U1.26 (IO1/TXD0)

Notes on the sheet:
230 V AC - mains section. Keep >= 8 mm creepage to everything else (milled slot under PS1).
Galvanic isolation: ESP side (GND) | spa side (GND_SPA), barrier under U2.
RS485 / Modbus RTU to the pump drives. Fit JP1 at the bus end only.
WT32-ETH01 plugs into two 1x13 female headers. 5 V only (never 5 V and 3V3 at once).

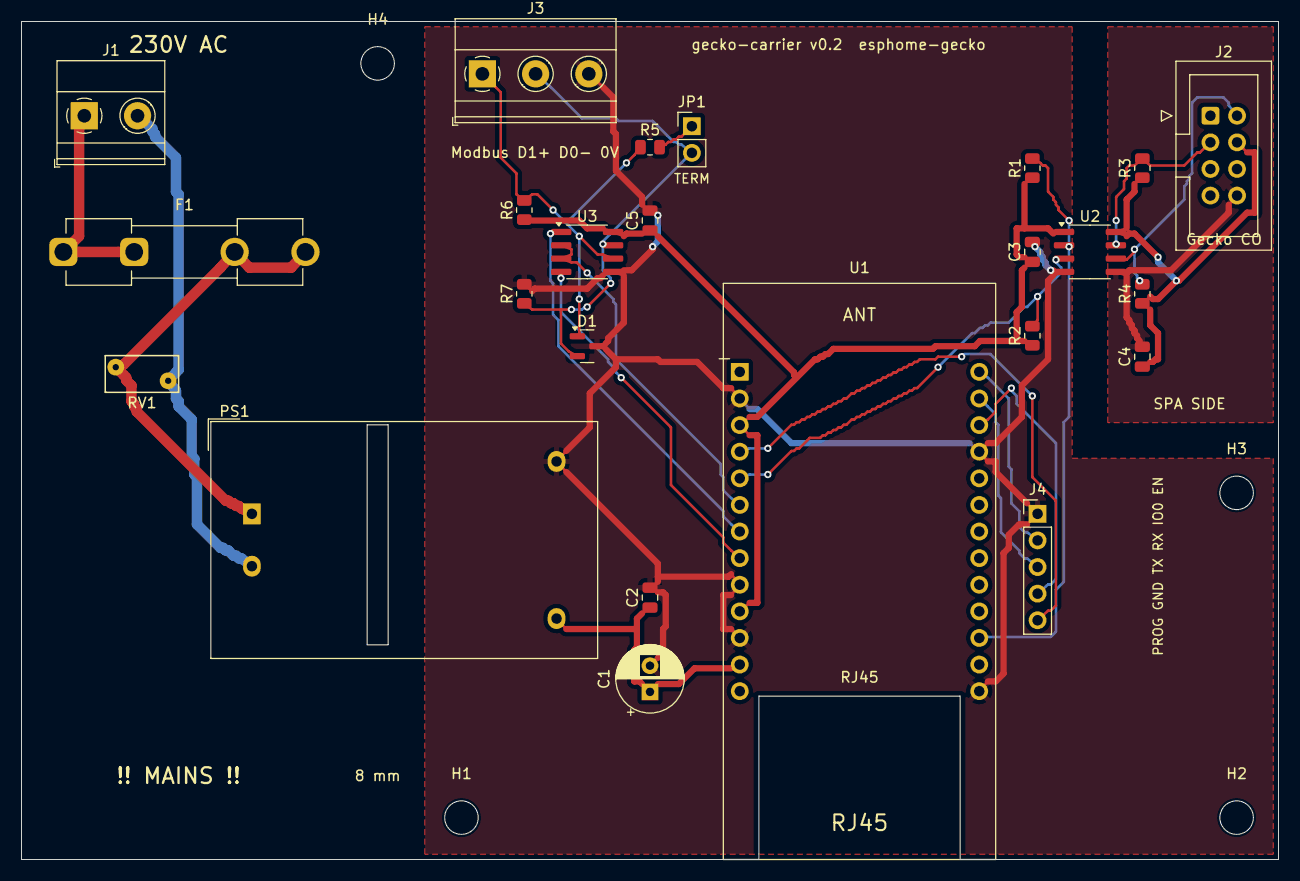
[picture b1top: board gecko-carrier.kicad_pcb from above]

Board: 2 copper layers, 120.0 x 80.0 mm, 28 parts (0 on the bottom side), 22 nets.

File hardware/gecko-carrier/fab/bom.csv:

Qty,References,Value,Footprint
1,C1,220uF 10V,CP_Radial_D6.3mm_P2.50mm
4,C2 C3 C4 C5,100nF,C_0805_2012Metric
1,D1,SM712,SOT-23
1,F1,T250mA 5x20,Fuseholder_Clip-5x20mm_Keystone_3517_Inline_P23.11x6.76mm_D1.70mm_Horizontal
4,H1 H2 H3 H4,M3,MountingHole_3.2mm_M3
1,J1,"230V AC (L, N)","TerminalBlock_Phoenix_MKDS-1,5-2-5.08_1x02_P5.08mm_Horizontal"
1,J2,Gecko CO port,IDC-Header_2x04_P2.54mm_Vertical
1,J3,Modbus: D1(A+) D0(B-) 0V,"TerminalBlock_Phoenix_MKDS-1,5-3-5.08_1x03_P5.08mm_Horizontal"
1,J4,PROG (GND TX RX IO0 EN),PinHeader_1x05_P2.54mm_Vertical
1,JP1,TERM (jumper),PinHeader_1x02_P2.54mm_Vertical
1,PS1,HLK-PM01 (5V 0.6A),Converter_ACDC_Hi-Link_HLK-PMxx
2,R1 R2,4k7,R_0805_2012Metric
2,R3 R4,4k7 DNP,R_0805_2012Metric
1,R5,120R,R_0805_2012Metric
2,R6 R7,680R,R_0805_2012Metric
1,RV1,275VAC 07D431K,RV_Disc_D7mm_W3.5mm_P5mm
1,U1,WT32-ETH01,WT32-ETH01_Socket
1,U2,ISO1540,SOIC-8_3.9x4.9mm_P1.27mm
1,U3,MAX3485,SOIC-8_3.9x4.9mm_P1.27mm
2,(for U1),1x13 female header 2.54mm,PinSocket_1x13_P2.54mm_Vertical

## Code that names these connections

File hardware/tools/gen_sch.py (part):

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    for num in ("1", "13", "15", "17", "18", "19", "20", "21", "22"):
        S.nc("U1", num)
    S.label("U1", "4", "EN")
    S.label("U1", "5", "SCL_ESP")
    S.label("U1", "6", "RS485_DE")
    S.label("U1", "7", "RS485_RO")
    S.label("U1", "8", "RS485_DI")
    S.label("U1", "16", "SDA_ESP")
    for u, j in (("26", "2"), ("25", "3"), ("24", "4")):
        W(("U1", u), ("J4", j))
    S.pwr("J4", "1", "GND", bend=True)
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    xl = 226.06
    W(sda1, (xl, sda1[1]))
    W(scl1, (xl, scl1[1]))
    S.label_at("SDA_ESP", (xl, sda1[1]), (-1, 0))
    S.label_at("SCL_ESP", (xl, scl1[1]), (-1, 0))
    W(("R1", "2"), (S.P("R1", "2")[0], sda1[1]))
    W(("R2", "2"), (S.P("R2", "2")[0], scl1[1]))  # crosses SDA without connecting
    S.pwr("R1", "1", "+3V3")
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        S.nc("J2", n)

    # ---- RS485 ----
    S.label("U3", "1", "RS485_RO", 15.24)
    re_, de = S.P("U3", "2"), S.P("U3", "3")
    W(re_, (re_[0] - 2.54, re_[1]), (de[0] - 2.54, de[1]))
    de_end = (de[0] - 15.24, de[1])
    W(de, de_end)
    S.label_at("RS485_DE", de_end, (-1, 0))
    S.label("U3", "4", "RS485_DI", 15.24)
    S.pwr("U3", "8", "+3V3")
    S.pwr("U3", "5", "GND")
    W(("U3", "6"), ("J3", "1"))
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    W(j2p, (xb, j2p[1]), (xb, yb))
    S.pwr("C5", "1", "+3V3")
    S.pwr("C5", "2", "GND")
    S.label("D1", "1", "RS485_A")
    S.label("D1", "2", "RS485_B")
    S.pwr("D1", "3", "GND", bend=True)
    x0 = S.P("U3", "6")[0]
    S.label_at("RS485_A", (x0 + 2.54, ya), (0, -1))
    S.label_at("RS485_B", (x0 + 5.08, yb), (0, 1))


def main():
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

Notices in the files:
README.md:
License:
MIT License - See LICENSE file for details.
